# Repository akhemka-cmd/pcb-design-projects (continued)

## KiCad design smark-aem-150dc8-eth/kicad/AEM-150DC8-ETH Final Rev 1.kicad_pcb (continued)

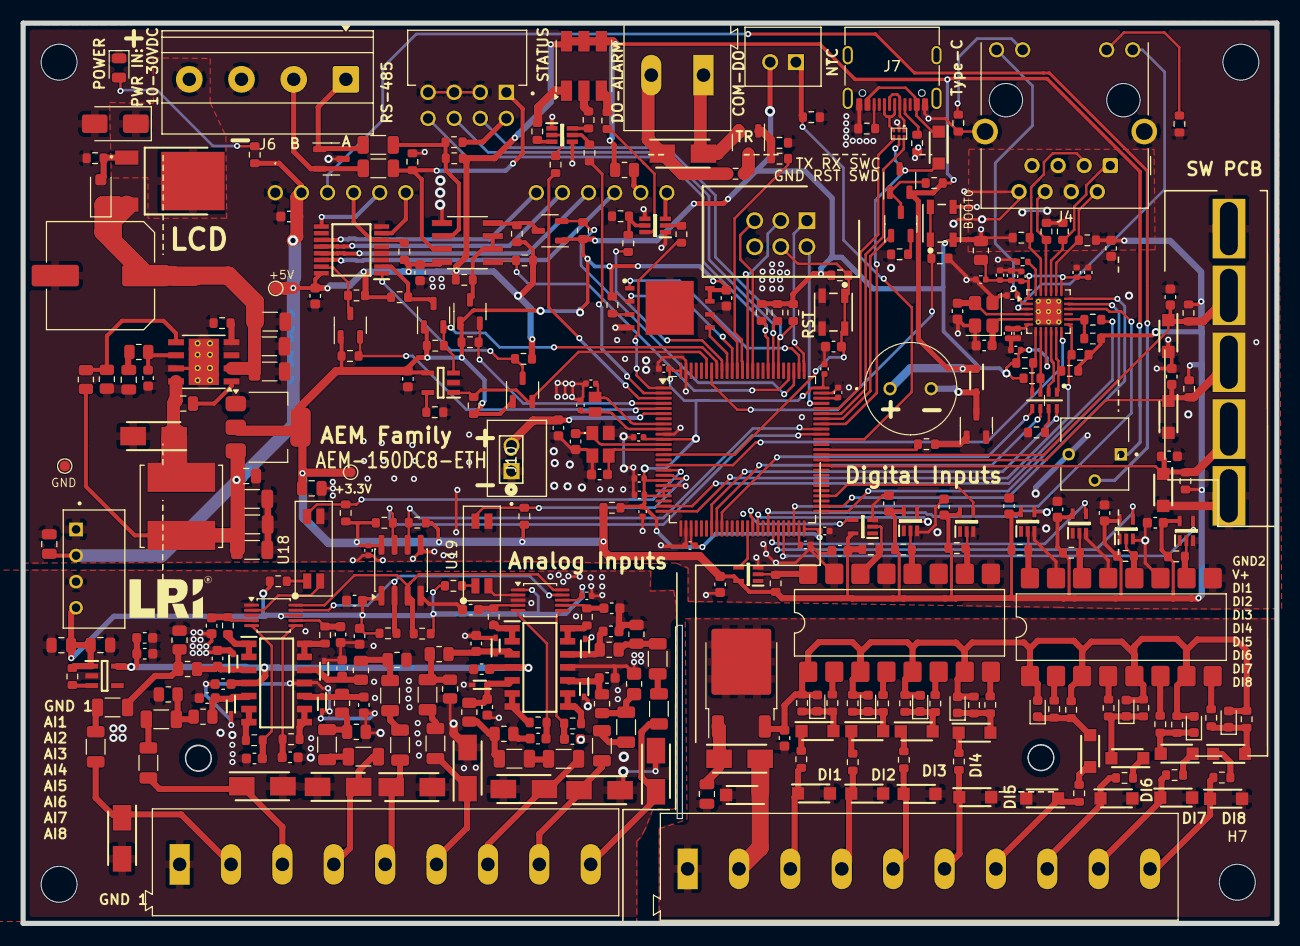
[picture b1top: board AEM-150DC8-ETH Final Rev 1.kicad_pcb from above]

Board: 2 copper layers, 122.0 x 87.6 mm, 360 parts (0 on the bottom side), 241 nets.

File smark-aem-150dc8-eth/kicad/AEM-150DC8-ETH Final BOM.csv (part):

#,Qty,Value,Reference,Footprint,Description,LCSC_Part,MPN,Manufacturer,PartLink,MANF_NUMBER
90,1,LCD 16x4,DS1,AEM-150DC8:NHD0416BZFLGBW,LCD Character Display Modules & Accessories STN- GRAY Transfl 87.0 x 60.0,,CH1604C,,,
56,1,Buzzer,BZ1,AEM-150DC8:QMB09B03,BUZZER MAGNETIC 2V~5V 9mm TH,C96256,QMB-09B-03,Huaneng,,
18,4,4.7K,"R120,R121,R122,R123",AEM-150DC8:R0603,,,,PANASONIC,,
107,2,1K,"R136,R142",AEM-150DC8:R0603,,,,PANASONIC,,
26,13,10K,"R101,R125,R126,R127,R128,R139,R140,R141,R143,R144,R152,R153,R236",AEM-150DC8:R0603,10kΩ ±5% 100mW 0603 Thick Film Resistor,C2907166,FRC0603J472 TS,FOJAN,,
76,1,FerriteBead,FB1,AEM-150DC8:R0805,Ferrite bead,,,,,
77,1,Screw_Terminal_01x02,J8,AEM-150DC8:TerminalBlock_2P_P5.08mm,"Generic screw terminal, single row, 01x02",C5188473,MX128L-5.08-02P-GN01-Cu-Y-A,MAX,,
57,1,100uF/63V,C2,Capacitor_SMD:C_Elec_10x10.2,CAP ALUM 100uF ±20% 63V SMD,C280414,RT1J101M1010,ROQANG,,
62,1,RJ45_Hanrun_HR911105A_Horizontal,J4,Connector_RJ:RJ45_Hanrun_HR911105A_Horizontal,CONN MOD JACK RJ45 TH,C12074,HR911105A,,,
129,1,USB_C_Receptacle_USB2.0_16P,J7,Connector_USB:USB_C_Receptacle_G-Switch_GT-USB-7010ASV,USB 2.0-only 16P Type-C Receptacle connector,C42400252,HYCW498-USBC16-735B,HOAUC,,
65,1,25Mhz Crystal,Y3,Crystal:Crystal_SMD_3225-4Pin_3.2x2.5mm,CRYSTAL 25MHz 12pF SMD,C9006,X322525MOB4SI,,,
49,1,SMAJ30A,D4,Diode_SMD:D_SMA,48.4VC Clamp 8.3A Ipp TVS DIODE DO-214AC(SMA),C908776,SMAJ30A,GOODWORK,,
73,1,BZT52C10,D8,Diode_SMD:D_SOD-123F,DIODE ZENER 10V 500mW SOD-123,C5182291,BZT52C10V,JUXING,,
68,1,RO-0505S_EHP,PS1,footprints:CONV_RO-0505S_H,DC/DC Converters - Through Hole 1W 05VIN 05VOUT CONV DC/DC,  C22372152 ,RO-0505S/EHP,RECOM,,
79,1,Screw_Terminal_01x02,J10,FT1:CONN2_M22-2010_HRW,"Generic screw terminal, single row, 01x02, script generated (kicad-library-utils/schlib/autogen/connector/)",,,,,
17,1,XL-5050RGBC,D55,LED_SMD:LED_RGB_5050-6,5050 RGB SMD LED,C2843868,XL-5050RGBC,XINGLIGHT,,
98,2,LTV-217,"U18,U19",LTV-217:LTV-217,Optocoupler DC-IN 1-CH Transistor DC-OUT 4-Pin SMD T/R,,"LTV-217-C-G,LTV217",,,LTV-217-C-G
89,1,LAN8742A,U27,Package_DFN_QFN:VQFN-24-1EP_4x4mm_P0.5mm_EP2.5x2.5mm_ThermalVias,"LAN8720 Ethernet PHY with RMII interface, QFN-24",,LAN8742A,,,
67,2,LTV-847S,"U3,U4",Package_DIP:SMDIP-16_W9.53mm,"DC Optocoupler, Vce 35V, CTR 50%, SMDIP-16",C114599,LTV-847S,LITEON,,
113,1,STM32F407VETx,U23,Package_QFP:LQFP-100_14x14mm_P0.5mm,"STMicroelectronics Arm Cortex-M4 MCU, 512KB flash, 192KB RAM, 168 MHz, 1.8-3.6V, 82 GPIO, LQFP100",C28730,STM32F407VET6,,,
83,1,ISO1540DR,U26,Package_SO:SOIC-8_3.9x4.9mm_P1.27mm,"I2C Isolator, 2.5 kVrms, Bidirectional clock and data, SOIC-8",,ISO1540DR,,,
42,1,TPS54360DDAR,U5,Package_SO:TI_SO-PowerPAD-8_ThermalVias,"3.5A, Step Down DC-DC Converter with Eco-mode, 4.5-60V Input Voltage, PowerSO-8",C44377,TPS54360DDAR,TI,,
122,2,ADS1115IDGS,"U24,U25",Package_SO:TSSOP-10_3x3mm_P0.5mm,"Ultra-Small, Low-Power, I2C-Compatible, 860-SPS, 16-Bit ADCs With Internal Reference, Oscillator, and Programmable Comparator, VSSOP-10",,ADS1115IDGS,,,
100,1,100K,R2,Resistor_SMD:R_0603_1608Metric,RES 100kΩ ±1% 100mW 0603,C2906980,FRC0603F1003TS,FOJAN,https://www.digikey.in/en/products/detail/yageo/RC0603FR-071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,
106,1,1K,R60,Resistor_SMD:R_0805_2012Metric,,,,PANASONIC,,
7,3,20.5K,"R57,R59,R61",Resistor_SMD:R_0805_2012Metric,,C161788,ERJPB6B1002V,PANASONIC,,
8,1,20.5K,R63,Resistor_SMD:R_0805_2012Metric_Pad1.20x1.40mm_HandSolder,,C161788,ERJPB6B1002V,PANASONIC,,
47,1,4.7uF/25V,C67,SMARKKicadLib:C0402,4.7uF ±20% 25V Ceramic Capacitor X5R 0402,C6119795,CGA0402X5R475M250GT,HRE,,
22,7,100nF,"C80,C115,C117,C119,C121,C122,C123",SMARKKicadLib:C0402,,C36911361,CGA0402X7R104M500GT,HRE,,
38,3,1uF,"C79,C81,C120",SMARKKicadLib:C0402,,C36911361,CGA0402X7R104M500GT,HRE,,
20,5,0.1uF,"C62,C65,C66,C69,C70",SMARKKicadLib:C0402,,,,HRE,https://www.digikey.in/en/products/detail/samsung-electro-me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 ,
32,2,12pF,"C73,C74",SMARKKicadLib:C0402,,,,HRE,,
28,2,10uF,"C64,C116",SMARKKicadLib:C0402,,,,HRE,https://www.digikey.in/en/products/detail/samsung-electro-me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 ,
50,1,6.8pF/100V,C17,SMARKKicadLib:C0603,6.8pF NP0 100V 0603 Ceramic Capacitors RoHS,C6117724,AC0603CRNPO0BN6R8,YAGEO,,
31,2,12pF,"C45,C46",SMARKKicadLib:C0603,12pF ±5% 50V Ceramic Capacitor C0G 0603,C45359931,CGA0603C0G120J500JT,HRE,,
37,4,1uF/10V,"C3,C56,C57,C58",SMARKKicadLib:C0603,1uF ±10% 10V Ceramic Capacitor X5R 0603,C20070307,CGA0603X5R105K100JT,HRE,,
27,1,10uF,C63,SMARKKicadLib:C0603,10uF ±10% 50V Ceramic Capacitor X7R 0603,C6119867,CGA0603X7R104K500JT,HRE,https://www.digikey.in/en/products/detail/samsung-electro-me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 ,
59,1,10uF/16V,C72,SMARKKicadLib:C0603,CAP CER 10uF 16V X5R 0603,,,,,
19,34,0.1uF,"C4,C5,C6,C7,C9,C13,C14,C15,C16,C19,C20,C21,C22,C24,C27,C28,C29,C30,C31,C32,C33,C34,C37,C38,C39,C40,C42,C48,C54,C55,C59,C60,C61,C75",SMARKKicadLib:C0603,0.1uF ±10% 50V Ceramic Capacitor X7R 0603,C6119867,,HRE,https://www.digikey.in/en/products/detail/samsung-electro-me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 ,
23,1,100nF/25V,C18,SMARKKicadLib:C0805,100nF ±10% 25V Ceramic Capacitor X7R 0805,C36911366,CGA0805X7R104K250KT,HRE,,
60,1,10uF/50V,C1,SMARKKicadLib:C0805,CAP CER 10uF 50V X5R 0805,C2932476,CL21A106KBYQNNE,Samsung Electro-Mechanics,,
58,3,10uF/16V,"C25,C36,C77",SMARKKicadLib:C0805,CAP CER 10uF 16V X5R 0805,C77075,GRM21BR61C106KE15L,FOJAN,,
46,1,4.7nF/50V,C12,SMARKKicadLib:C0805,4.7nF ±20% 50V Ceramic Capacitor X7R 0805,C5375827,TCC0805X7R472M500DT,CCTC,,
36,3,1uF/100V,"C8,C10,C11",SMARKKicadLib:C1206,1uF ±10% 100V Ceramic Capacitor X7R 1206,C13832,CL31B105KCHNNNE,Samsung Electro-Mechanics,,
61,3,47uF/10V,"C23,C26,C35",SMARKKicadLib:C1206,CAP CER 47uF 10V X5R 1206,C5449028,TCC1206X5R476K100HT,CCTC,,
16,1,33R,RN1,SMARKKicadLib:CAT16-1206_8L,"4 resistor network, parallel topology, split",,CAT16-1206_8L,,,
55,1,CONN_03X2SHROUD,J5,SMARKKicadLib:CONN_2X3-SHROUDED_HEADER,"Box Header, Vertical, 6 Pos",C601936,321006SG0ABK00A01,JILN,https://www.digikey.in/en/products/detail/adam-tech/BHR-06-V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,
52,1,B340A-13-F,D6,SMARKKicadLib:DO-214AC,80A 1 Independent 40V 500mV@3A 3A SMA(DO-214AC) Single Diodes RoHS,C85098,B340A-13-F,DIODES,https://www.digikey.in/en/products/detail/diodes-incorporate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,
117,8,SMAJ160A,"D11,D12,D13,D14,D37,D38,D39,D40",SMARKKicadLib:DO-214AC,TVS DIODE 160VWM 259VC DO-214AC(SMA),C2984997,SMAJ160A,GOODWORK,,
48,1,SMAJ26A,D49,SMARKKicadLib:DO-214AC,42.1VC Clamp 9.5A@10/1000us Ipp DO-214AC(SMA),C42370520,SMAJ26A,TECH PUBLIC,,
72,1,SS54,D41,SMARKKicadLib:DO-214AC,Diode Independent 40V 5A Surface Mount SMA(DO-214AC),C2988633,UMW SS54A,UMW,,
121,1,PRTR5V0U2F,D50,SMARKKicadLib:FNL6_SOT886_NEX,TVS DIODE 5.5VWM 6XSON,C478118,"PRTR5V0U2F,115",Nexperia USA Inc.,https://www.digikey.in/en/products/detail/nexperia-usa-inc/P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,
1,1,MNR8065T100MT,L1,SMARKKicadLib:IND_SRN8040TA,,,MNR8065T100MT,MetalLions,,
63,1,Conn_01x02,J1,SMARKKicadLib:JST_B2B-XH-A,Connector Header 2 position 2.54mm Pitch 3A Through Hole -25℃~+85℃,C42391660,HX-XH2.54-2PZZ,hanxia,,
78,1,Screw_Terminal_01x02,J9,SMARKKicadLib:JST_B2B-XH-A,"Generic screw terminal, single row, 01x02, script generated (kicad-library-utils/schlib/autogen/connector/)",,,,,
91,8,LED,"D1,D2,D5,D7,D9,D10,D15,D16",SMARKKicadLib:LED_0603_1608Metric,LED RED CLEAR CHIP SMD 0603,C965799,XL-1608SURC-06,XINGLIGHT,https://www.digikey.in/en/products/detail/liteon/LTST-C190KR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,
92,1,LED,D46,SMARKKicadLib:LED_0805_2012Metric,LED RED WATER CLEAR 0805 SMD,C22371391,XL-2012SURC,XINGLIGHT,,
54,2,MountingHole,"H2,H3",SMARKKicadLib:MountingHole_2.5mm,"Board Spacers, Standoffs RoHS",C123695,HP-20M3*20,HIWA,,
99,1,10K,RV1,SMARKKicadLib:Pot_TRIM_3362P-1-103LF,POT 10kΩ Through Hole,C118956,3362P-1-103LF,BOCHEN,,
101,2,100K,"R89,R103",SMARKKicadLib:R0603,RES 100kΩ ±1% 100mW 0603,C2906980,FRC0603F1003TS,FOJAN,https://www.digikey.in/en/products/detail/yageo/RC0603FR-071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,
103,1,150R,R108,SMARKKicadLib:R0603,RES 150Ω ±1% 100mW 0603,C2906994,FRC0603F1500TS,FOJAN,,
33,1,191K,R44,SMARKKicadLib:R0603,191kΩ ±1% 100mW 0603 Thick Film Resistor,C2974031,FRC0603F1913TS,FOJAN,,
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
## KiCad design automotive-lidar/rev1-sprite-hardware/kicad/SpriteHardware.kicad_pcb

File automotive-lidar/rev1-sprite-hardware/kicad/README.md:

# Hardware

KiCad files for Project Sprite

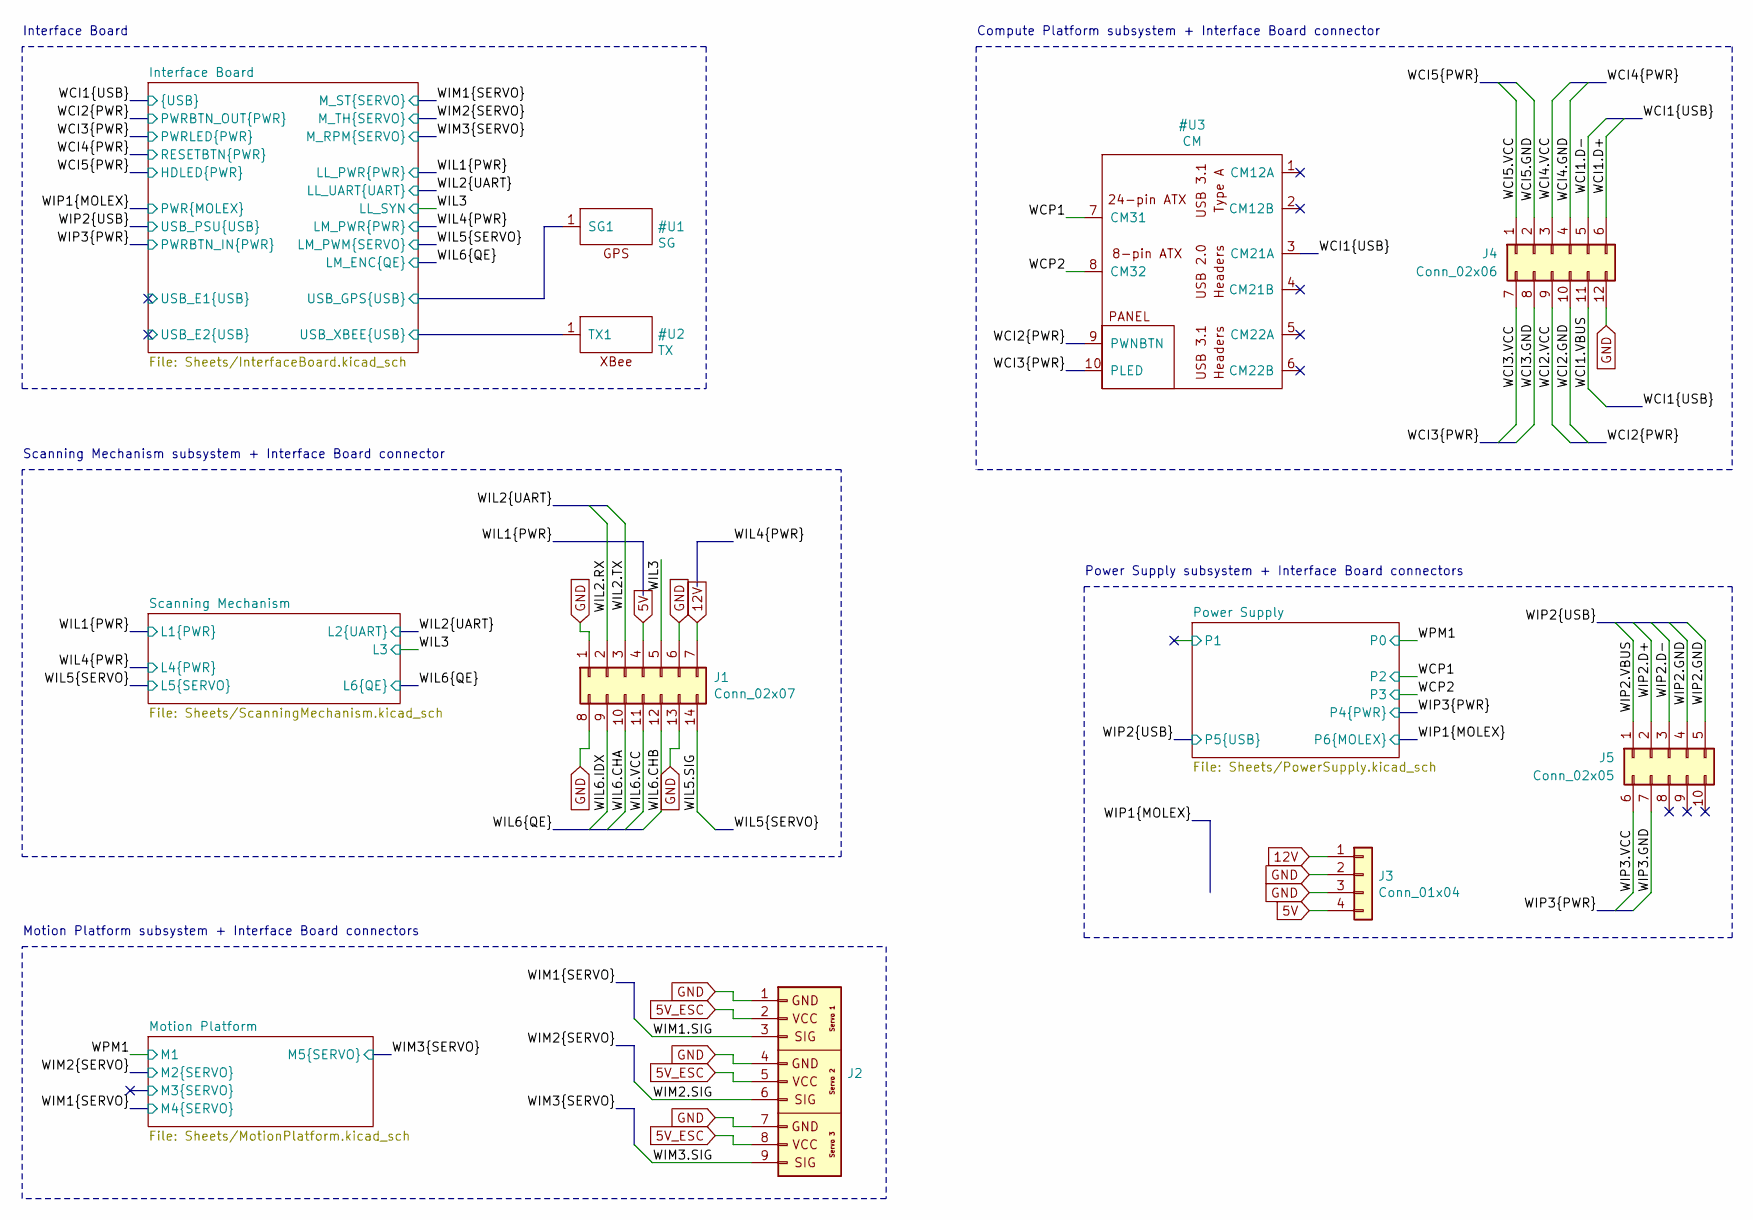
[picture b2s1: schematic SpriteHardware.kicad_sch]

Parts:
J1: Conn_02x07; 901303314
J2: Conn_03x03_Servo
J3: Conn_01x04; 641737-1
J4: Conn_02x06; 901303312
J5: Conn_02x05; 901303310

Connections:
5V: J1.4, J3.4; also elsewhere on the board
5V_ESC: J2.2 (VCC1), J2.5 (VCC2), J2.8 (VCC3); also elsewhere on the board
12V: J1.7, J3.1
/WCI1.D+: J4.6; also elsewhere on the board
/WCI1.D-: J4.5; also elsewhere on the board
/WCI1.VBUS: J4.11; also elsewhere on the board
/WCI3.GND: J4.8; also elsewhere on the board
/WCI3.VCC: J4.7; also elsewhere on the board
/WCI4.GND: J4.4; also elsewhere on the board
/WCI4.VCC: J4.3; also elsewhere on the board
/WCI5.GND: J4.2; also elsewhere on the board
/WCI5.VCC: J4.1; also elsewhere on the board
/WIL2.RX: J1.2; also elsewhere on the board
/WIL2.TX: J1.3; also elsewhere on the board
/WIL3: J1.5; also elsewhere on the board
/WIL5.SIG: J1.14; also elsewhere on the board
/WIL6.CHA: J1.10; also elsewhere on the board
/WIL6.CHB: J1.12; also elsewhere on the board
/WIL6.IDX: J1.9; also elsewhere on the board
/WIL6.VCC: J1.11; also elsewhere on the board
/WIM1.SIG: J2.3 (SIG1); also elsewhere on the board
/WIM2.SIG: J2.6 (SIG2); also elsewhere on the board
/WIM3.SIG: J2.9 (SIG3); also elsewhere on the board
/WIP2.D+: J5.2; also elsewhere on the board
/WIP2.D-: J5.3; also elsewhere on the board
/WIP2.GND: J5.4, J5.5
/WIP2.VBUS: J5.1; also elsewhere on the board
GND: J1.1, J1.6, J1.8, J1.13, J2.1 (GND1), J2.4 (GND2), J2.7 (GND3), J3.2, J3.3, J4.12; also elsewhere on the board

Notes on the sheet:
Motion Platform subsystem + Interface Board connectors
Compute Platform subsystem + Interface Board connector
Interface Board
Power Supply subsystem + Interface Board connectors
Scanning Mechanism subsystem + Interface Board connector

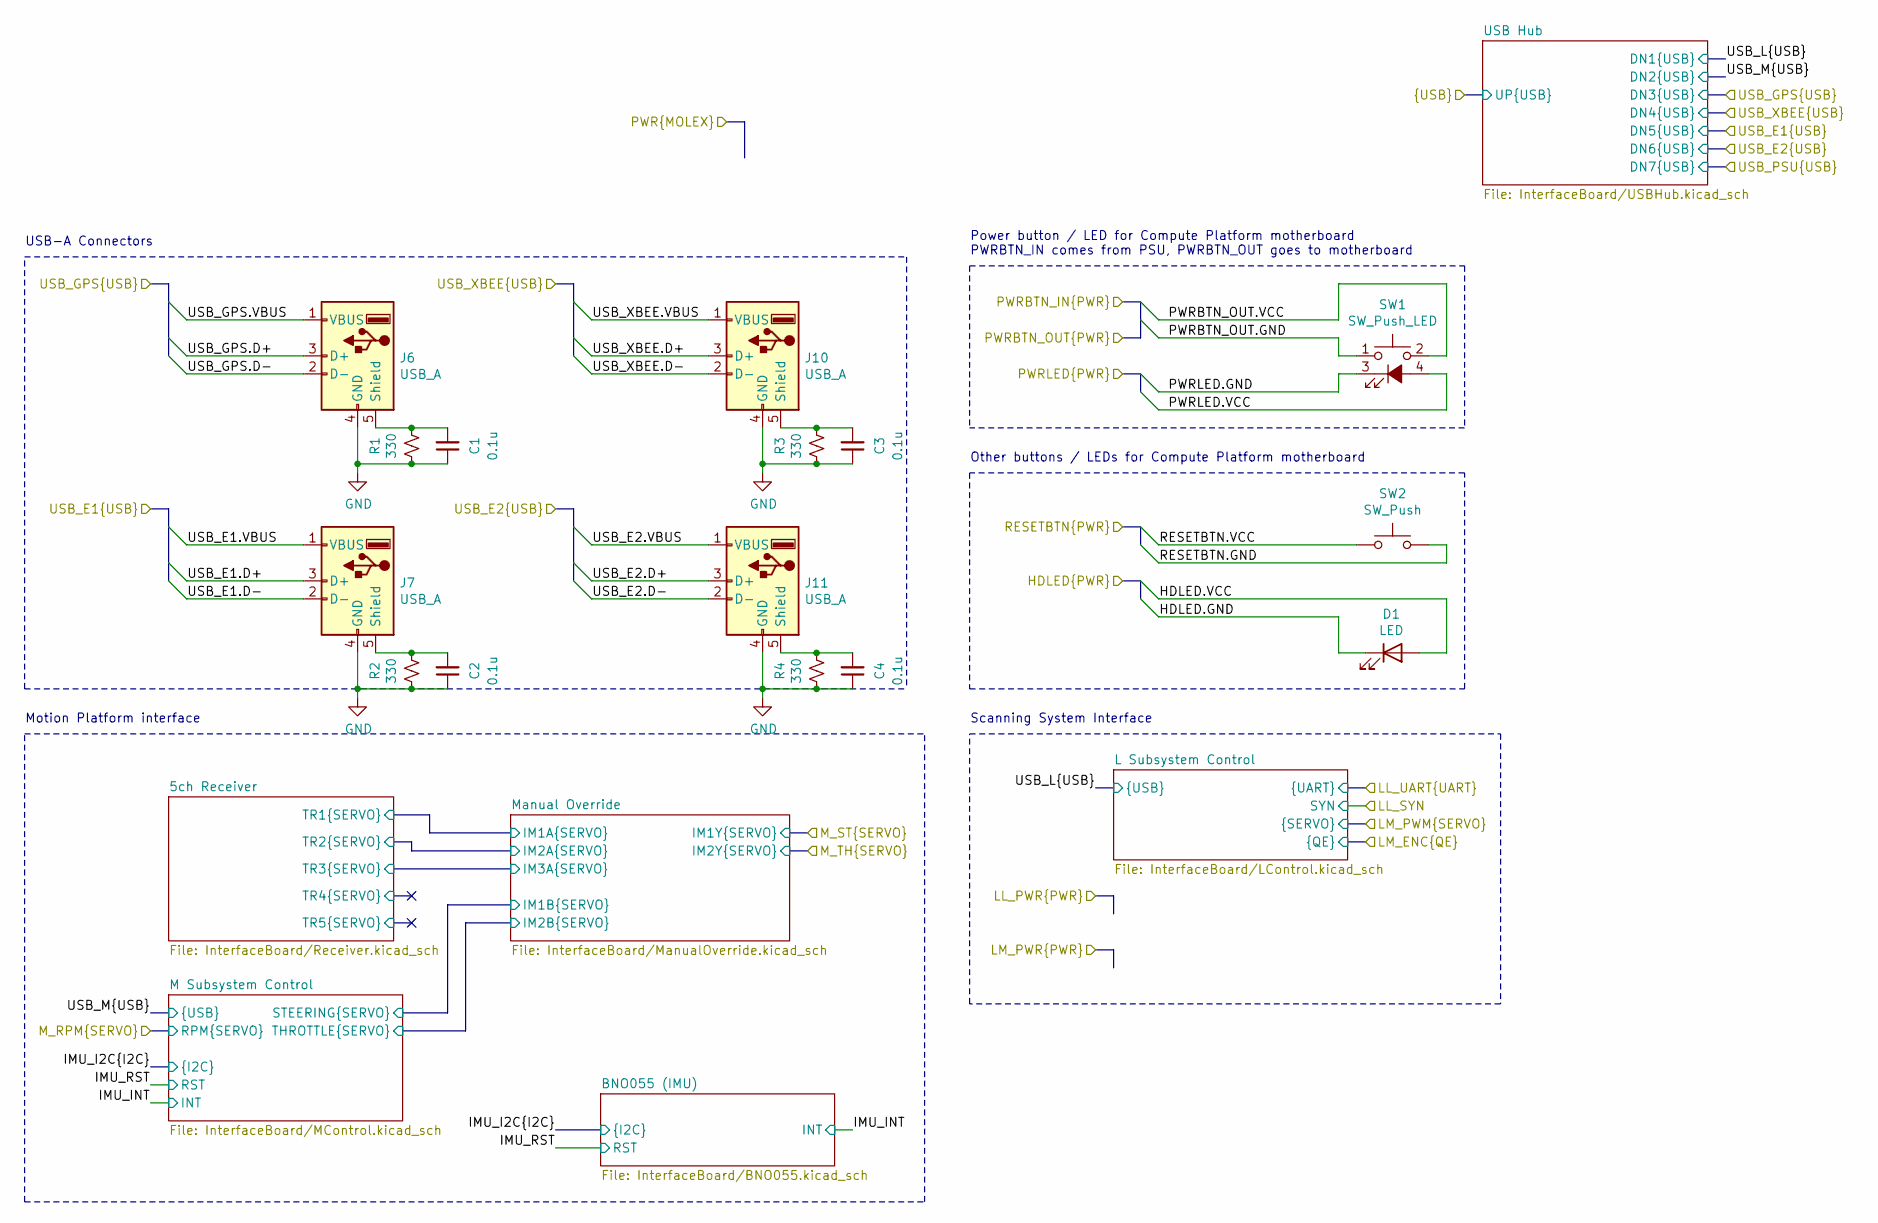
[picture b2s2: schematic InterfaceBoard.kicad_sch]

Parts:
C1, C2, C3, C4: 0.1u; C_0603_1608Metric_Pad1.05x0.95mm_HandSolder
D1: LED; LED_0603_1608Metric_Pad1.05x0.95mm_HandSolder
J6, J7, J10, J11: USB_A; USB_A_Female_Vertical_RA_73725-0110BLF
R1, R2, R3, R4: 330; R_0603_1608Metric_Pad1.05x0.95mm_HandSolder
SW1: SW_Push_LED; 3105
SW2: SW_Push; SW_SPST_PTS645

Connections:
/USB_E1.D+: J7.3 (D+); also elsewhere on the board
/USB_E1.D-: J7.2 (D-); also elsewhere on the board
/USB_E1.VBUS: J7.1 (VBUS); also elsewhere on the board
/USB_E2.D+: J11.3 (D+); also elsewhere on the board
/USB_E2.D-: J11.2 (D-); also elsewhere on the board
/USB_E2.VBUS: J11.1 (VBUS); also elsewhere on the board
/USB_GPS.D+: J6.3 (D+); also elsewhere on the board
/USB_GPS.D-: J6.2 (D-); also elsewhere on the board
/USB_GPS.VBUS: J6.1 (VBUS); also elsewhere on the board
/USB_XBEE.D+: J10.3 (D+); also elsewhere on the board
/USB_XBEE.D-: J10.2 (D-); also elsewhere on the board
/USB_XBEE.VBUS: J10.1 (VBUS); also elsewhere on the board
/WCI3.GND: SW1.3 (K); also elsewhere on the board
/WCI3.VCC: SW1.4 (A); also elsewhere on the board
/WCI4.GND: SW2.2; also elsewhere on the board
/WCI4.VCC: SW2.1; also elsewhere on the board
/WCI5.GND: D1.1 (K); also elsewhere on the board
/WCI5.VCC: D1.2 (A); also elsewhere on the board
GND: C1.1, C2.1, C3.1, C4.1, J6.4 (GND), J7.4 (GND), J10.4 (GND), J11.4 (GND), R1.1, R2.1, R3.1, R4.1; also elsewhere on the board
unnamed: C1.2, J6.5 (Shield), R1.2
unnamed: C2.2, J7.5 (Shield), R2.2
unnamed: C3.2, J10.5 (Shield), R3.2
unnamed: C4.2, J11.5 (Shield), R4.2

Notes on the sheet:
Scanning System Interface
Power button / LED for Compute Platform motherboard PWRBTN_IN comes from PSU, PWRBTN_OUT goes to motherboard
USB-A Connectors
Other buttons / LEDs for Compute Platform motherboard
Motion Platform interface

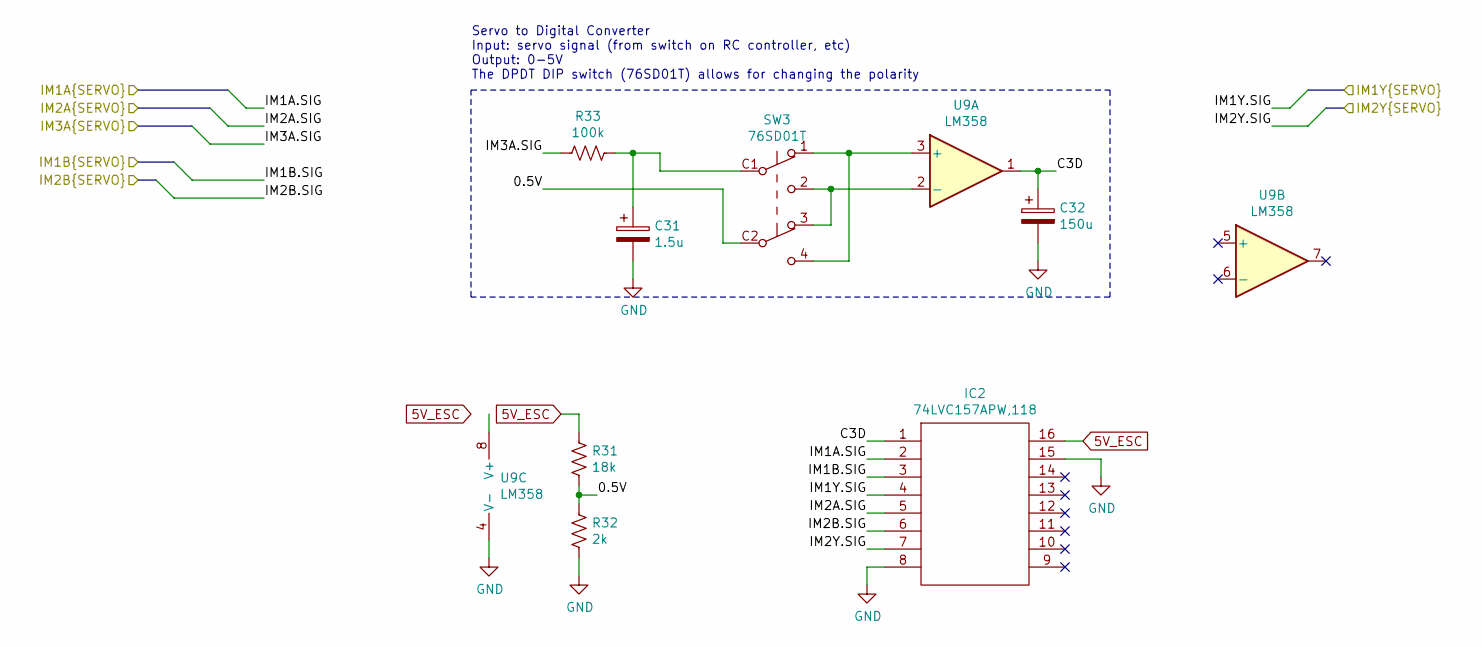
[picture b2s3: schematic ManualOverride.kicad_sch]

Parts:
C31: 1.5u; C_0805_2012Metric_Pad1.15x1.40mm_HandSolder
C32: 150u; CP_Elec_6.3x5.4_Nichicon
IC2: 74LVC157APW,118; SOP65P640X110-16N; Mouser Part Number 771-74LVC157APW-T
R31: 18k; R_0603_1608Metric_Pad1.05x0.95mm_HandSolder
R32: 2k; R_0603_1608Metric_Pad1.05x0.95mm_HandSolder
R33: 100k; R_0603_1608Metric_Pad1.05x0.95mm_HandSolder
SW3: 76SD01T
U9: LM358; SOIC127P600X175-8N

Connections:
5V_ESC: IC2.16, R31.1; also elsewhere on the board
/Interface Board/IM2A.SIG: IC2.5; also elsewhere on the board
/Interface Board/IM3A.SIG: R33.2; also elsewhere on the board
/Interface Board/Manual Override/0.5V: R31.2, R32.1, SW3.C2 (B)
/Interface Board/Manual Override/C3D: C32.1, IC2.1, U9.1
/Interface Board/STEERING.SIG: IC2.3; also elsewhere on the board
/Interface Board/THROTTLE.SIG: IC2.6; also elsewhere on the board
/Interface Board/TR1.SIG: IC2.2; also elsewhere on the board
/WIM1.SIG: IC2.4; also elsewhere on the board
/WIM2.SIG: IC2.7; also elsewhere on the board
GND: C31.2, C32.2, IC2.8, IC2.15, R32.2, U9.4 (V-); also elsewhere on the board
unnamed: C31.1, R33.1, SW3.C1 (B)
unnamed: SW3.1 (A), SW3.4 (C), U9.3 (+)
unnamed: SW3.2 (C), SW3.3 (A), U9.2 (-)

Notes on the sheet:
Servo to Digital Converter Input: servo signal (from switch on RC controller, etc) Output: 0-5V The DPDT DIP switch (76SD01T) allows for changing the polarity

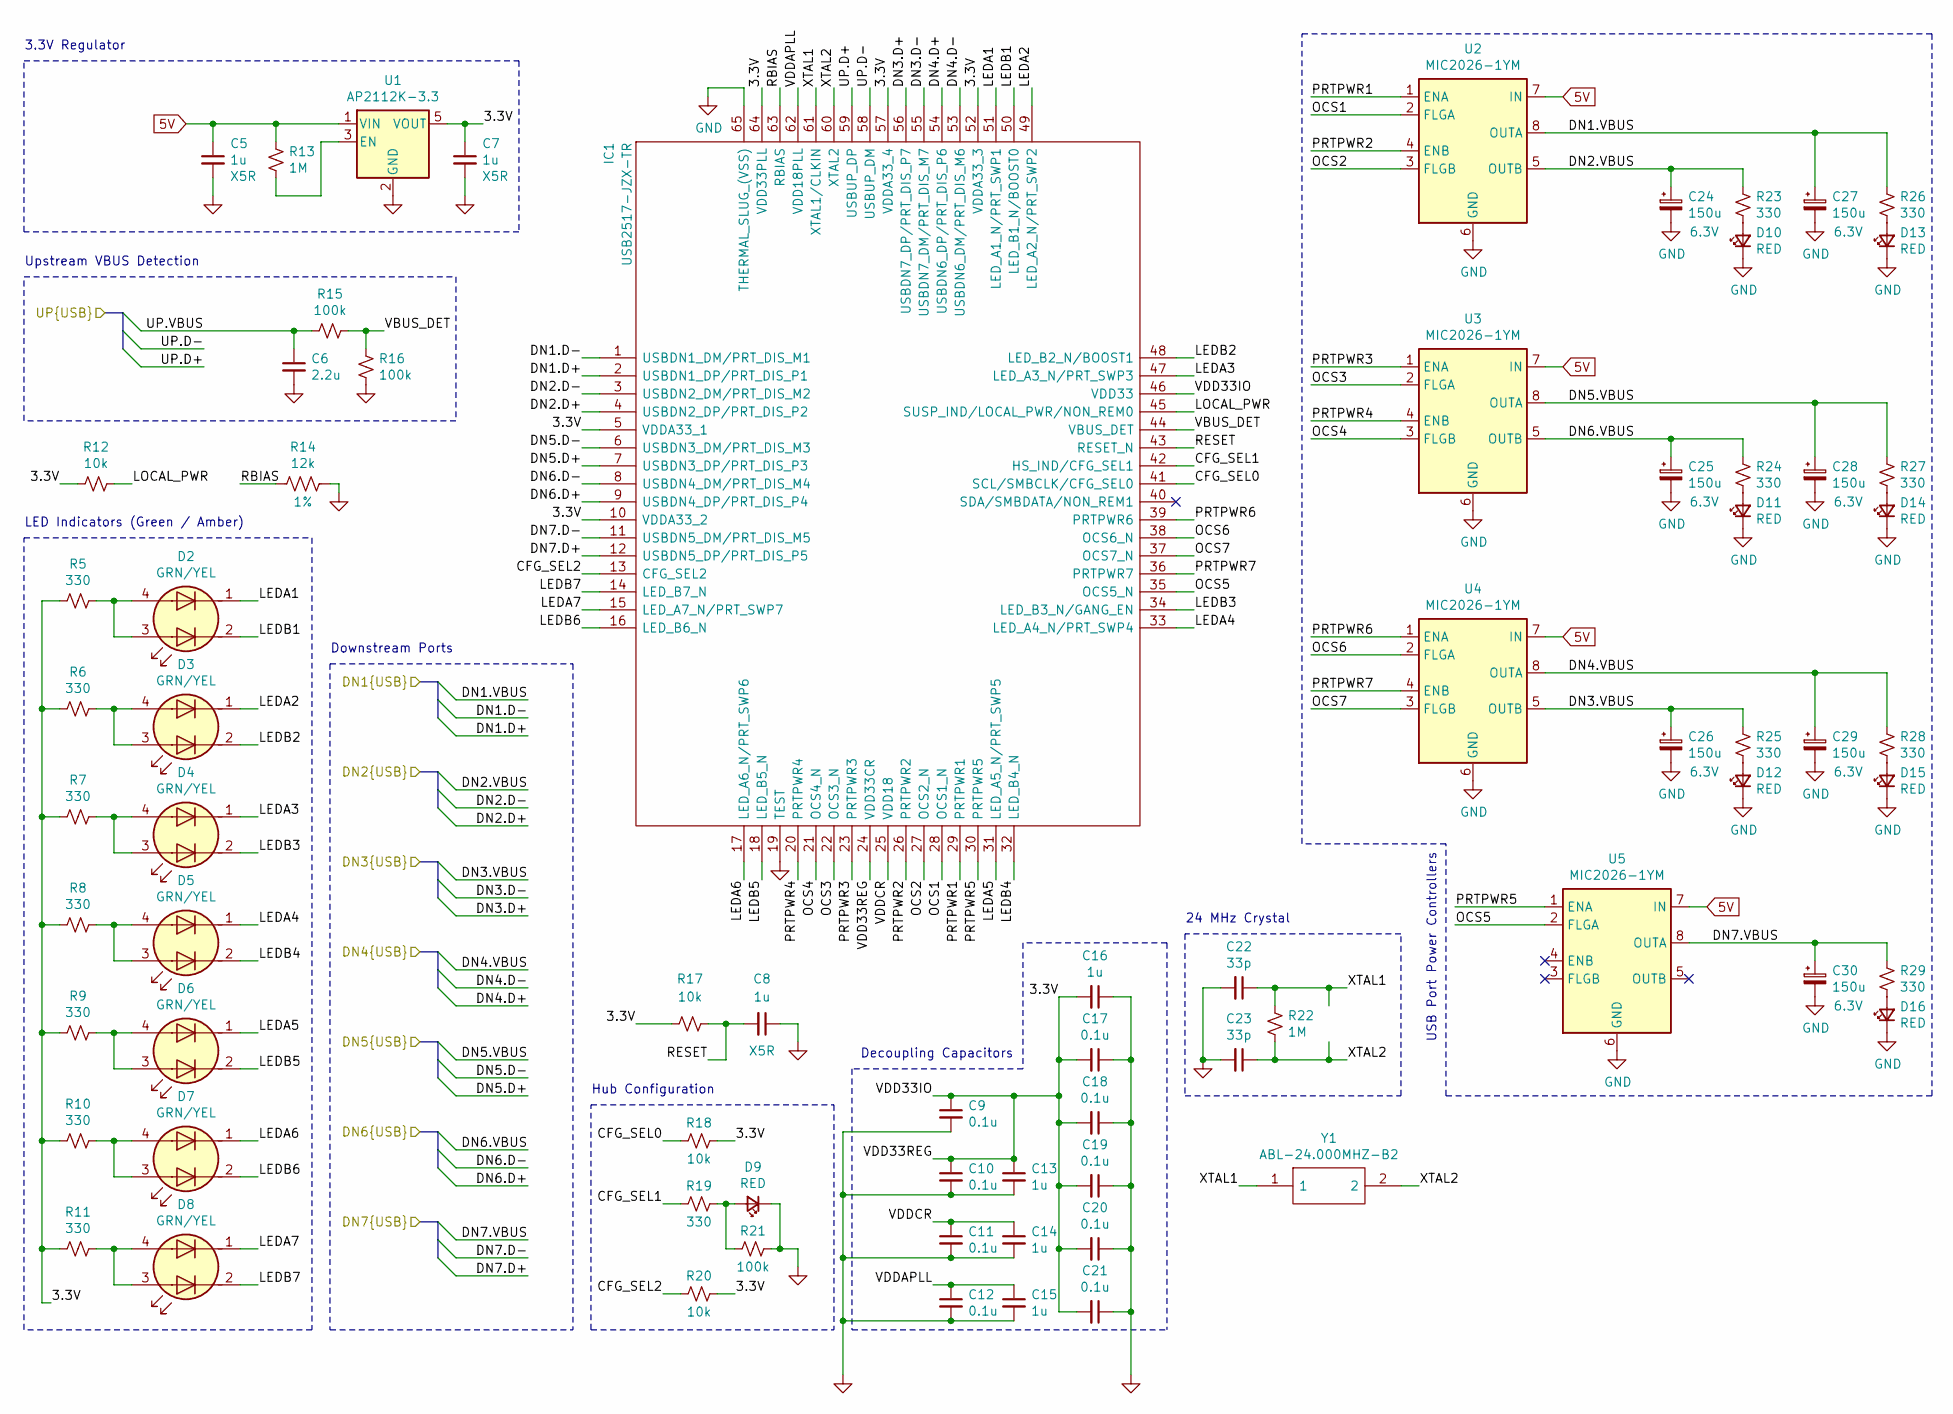
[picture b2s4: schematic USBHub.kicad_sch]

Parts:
C5, C7, C13, C14, C15, C16: 1u; C_0603_1608Metric_Pad1.05x0.95mm_HandSolder
C6: 2.2u; C_0603_1608Metric_Pad1.05x0.95mm_HandSolder
C8: 1u; C_0603_1608Metric_Pad1.05x0.95mm_HandSolder; Rating X5R
C9, C10, C11, C12, C17, C18, C19, C20, C21: 0.1u; C_0603_1608Metric_Pad1.05x0.95mm_HandSolder
C22, C23: 33p; C_0603_1608Metric_Pad1.05x0.95mm_HandSolder
C24, C25, C26, C27, C28, C29, C30: 150u; CP_Elec_6.3x5.4_Nichicon; Voltage 6.3V
D2, D3, D4, D5, D6, D7, D8: GRN/YEL; 156125YV73000
D9, D10, D11, D12, D13, D14, D15, D16: RED; LED_0603_1608Metric_Pad1.05x0.95mm_HandSolder
IC1: USB2517-JZX-TR; QFN50P900X900X100-65N-D; Mouser Part Number 579-USB2517-JZX-TR
R5, R6, R7, R8, R9, R10, R11, R19, R23, R24, R25, R26, R27, R28, R29: 330; R_0603_1608Metric_Pad1.05x0.95mm_HandSolder
R12, R17, R18, R20: 10k; R_0603_1608Metric_Pad1.05x0.95mm_HandSolder
R13, R22: 1M; R_0603_1608Metric_Pad1.05x0.95mm_HandSolder
R14: 12k; R_0603_1608Metric_Pad1.05x0.95mm_HandSolder; Tolerance 1%
R15, R16, R21: 100k; R_0603_1608Metric_Pad1.05x0.95mm_HandSolder
U1: AP2112K-3.3; SOT-23-5
U2, U3, U4, U5: MIC2026-1YM; SOIC-8_3.9x4.9mm_P1.27mm
Y1: ABL-24.000MHZ-B2; ABL110592MHZB2; Manufacturer_Part_Number ABL-24.000MHZ-B2; Mouser Part Number 815-ABL-24-B2

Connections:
5V: C5.1, R13.2, U1.1 (VIN), U2.7 (IN), U3.7 (IN), U4.7 (IN), U5.7 (IN); also elsewhere on the board
/Interface Board/USB Hub/3.3V: C7.1, C9.1, C10.1, C13.1, C16.2, C17.2, C18.2, C19.2, C20.2, C21.2, IC1.5 (VDDA33_1), IC1.10 (VDDA33_2), IC1.24 (VDD33CR), IC1.46 (VDD33), IC1.52 (VDDA33_3), IC1.57 (VDDA33_4), IC1.64 (VDD33PLL), R5.2, R6.2, R7.2, R8.2, R9.2, R10.2, R11.2, R12.2, R17.2, R18.1, R20.1, U1.5 (VOUT)
/Interface Board/USB Hub/CFG_SEL0: IC1.41 (SCL/SMBCLK/CFG_SEL0), R18.2
/Interface Board/USB Hub/CFG_SEL1: IC1.42 (HS_IND/CFG_SEL1), R19.2
/Interface Board/USB Hub/CFG_SEL2: IC1.13 (CFG_SEL2), R20.2
/Interface Board/USB Hub/LEDA1: D2.1 (A2), IC1.51 (LED_A1_N/PRT_SWP1)
/Interface Board/USB Hub/LEDA2: D3.1 (A2), IC1.49 (LED_A2_N/PRT_SWP2)
/Interface Board/USB Hub/LEDA3: D4.1 (A2), IC1.47 (LED_A3_N/PRT_SWP3)
/Interface Board/USB Hub/LEDA4: D5.1 (A2), IC1.33 (LED_A4_N/PRT_SWP4)
/Interface Board/USB Hub/LEDA5: D6.1 (A2), IC1.31 (LED_A5_N/PRT_SWP5)
/Interface Board/USB Hub/LEDA6: D7.1 (A2), IC1.17 (LED_A6_N/PRT_SWP6)
/Interface Board/USB Hub/LEDA7: D8.1 (A2), IC1.15 (LED_A7_N/PRT_SWP7)
/Interface Board/USB Hub/LEDB1: D2.2 (A1), IC1.50 (LED_B1_N/BOOST0)
/Interface Board/USB Hub/LEDB2: D3.2 (A1), IC1.48 (LED_B2_N/BOOST1)
/Interface Board/USB Hub/LEDB3: D4.2 (A1), IC1.34 (LED_B3_N/GANG_EN)
/Interface Board/USB Hub/LEDB4: D5.2 (A1), IC1.32 (LED_B4_N)
/Interface Board/USB Hub/LEDB5: D6.2 (A1), IC1.18 (LED_B5_N)
/Interface Board/USB Hub/LEDB6: D7.2 (A1), IC1.16 (LED_B6_N)
/Interface Board/USB Hub/LEDB7: D8.2 (A1), IC1.14 (LED_B7_N)
/Interface Board/USB Hub/LOCAL_PWR: IC1.45 (SUSP_IND/LOCAL_PWR/NON_REM0), R12.1
/Interface Board/USB Hub/OCS1: IC1.28 (OCS1_N), U2.2 (FLGA)
/Interface Board/USB Hub/OCS2: IC1.27 (OCS2_N), U2.3 (FLGB)
/Interface Board/USB Hub/OCS3: IC1.22 (OCS3_N), U3.2 (FLGA)
/Interface Board/USB Hub/OCS4: IC1.21 (OCS4_N), U3.3 (FLGB)
/Interface Board/USB Hub/OCS5: IC1.35 (OCS5_N), U5.2 (FLGA)
/Interface Board/USB Hub/OCS6: IC1.38 (OCS6_N), U4.2 (FLGA)
/Interface Board/USB Hub/OCS7: IC1.37 (OCS7_N), U4.3 (FLGB)
/Interface Board/USB Hub/PRTPWR1: IC1.29 (PRTPWR1), U2.1 (ENA)
/Interface Board/USB Hub/PRTPWR2: IC1.26 (PRTPWR2), U2.4 (ENB)
/Interface Board/USB Hub/PRTPWR3: IC1.23 (PRTPWR3), U3.1 (ENA)
/Interface Board/USB Hub/PRTPWR4: IC1.20 (PRTPWR4), U3.4 (ENB)
/Interface Board/USB Hub/PRTPWR5: IC1.30 (PRTPWR5), U5.1 (ENA)
/Interface Board/USB Hub/PRTPWR6: IC1.39 (PRTPWR6), U4.1 (ENA)
/Interface Board/USB Hub/PRTPWR7: IC1.36 (PRTPWR7), U4.4 (ENB)
/Interface Board/USB Hub/RBIAS: IC1.63 (RBIAS), R14.2
/Interface Board/USB Hub/RESET: C8.2, IC1.43 (RESET_N), R17.1
/Interface Board/USB Hub/VBUS_DET: IC1.44 (VBUS_DET), R15.1, R16.2
/Interface Board/USB Hub/VDDAPLL: C12.1, C15.1, IC1.62 (VDD18PLL)
/Interface Board/USB Hub/VDDCR: C11.1, C14.1, IC1.25 (VDD18)
/Interface Board/USB Hub/XTAL1: C22.1, IC1.61 (XTAL1/CLKIN), R22.1, Y1.1
/Interface Board/USB Hub/XTAL2: C23.1, IC1.60 (XTAL2), R22.2, Y1.2
/Interface Board/USB_L.D+: IC1.2 (USBDN1_DP/PRT_DIS_P1); also elsewhere on the board
/Interface Board/USB_L.D-: IC1.1 (USBDN1_DM/PRT_DIS_M1); also elsewhere on the board
/Interface Board/USB_M.D+: IC1.4 (USBDN2_DP/PRT_DIS_P2); also elsewhere on the board
/Interface Board/USB_M.D-: IC1.3 (USBDN2_DM/PRT_DIS_M2); also elsewhere on the board
/USB_E1.D+: IC1.7 (USBDN3_DP/PRT_DIS_P3); also elsewhere on the board
/USB_E1.D-: IC1.6 (USBDN3_DM/PRT_DIS_M3); also elsewhere on the board
/USB_E1.VBUS: C28.1, R27.2, U3.8 (OUTA); also elsewhere on the board
/USB_E2.D+: IC1.9 (USBDN4_DP/PRT_DIS_P4); also elsewhere on the board
/USB_E2.D-: IC1.8 (USBDN4_DM/PRT_DIS_M4); also elsewhere on the board
/USB_E2.VBUS: C25.1, R24.2, U3.5 (OUTB); also elsewhere on the board
/USB_GPS.D+: IC1.56 (USBDN7_DP/PRT_DIS_P7); also elsewhere on the board
/USB_GPS.D-: IC1.55 (USBDN7_DM/PRT_DIS_M7); also elsewhere on the board
/USB_GPS.VBUS: C26.1, R25.2, U4.5 (OUTB); also elsewhere on the board
/USB_XBEE.D+: IC1.54 (USBDN6_DP/PRT_DIS_P6); also elsewhere on the board
/USB_XBEE.D-: IC1.53 (USBDN6_DM/PRT_DIS_M6); also elsewhere on the board
/USB_XBEE.VBUS: C29.1, R28.2, U4.8 (OUTA); also elsewhere on the board
/WCI1.D+: IC1.59 (USBUP_DP); also elsewhere on the board
/WCI1.D-: IC1.58 (USBUP_DM); also elsewhere on the board
/WCI1.VBUS: C6.1, R15.2; also elsewhere on the board
/WIL6.VCC: C27.1, R26.2, U2.8 (OUTA); also elsewhere on the board
/WIM3.VCC: C24.1, R23.2, U2.5 (OUTB); also elsewhere on the board
/WIP2.D+: IC1.12 (USBDN5_DP/PRT_DIS_P5); also elsewhere on the board
/WIP2.D-: IC1.11 (USBDN5_DM/PRT_DIS_M5); also elsewhere on the board
/WIP2.VBUS: C30.1, R29.2, U5.8 (OUTA); also elsewhere on the board
GND: C5.2, C6.2, C7.2, C8.1, C9.2, C10.2, C11.2, C12.2, C13.2, C14.2, C15.2, C16.1, C17.1, C18.1, C19.1, C20.1, C21.1, C22.2, C23.2, C24.2, C25.2, C26.2, C27.2, C28.2, C29.2, C30.2, D9.1 (K), D10.1 (K), D11.1 (K), D12.1 (K), D13.1 (K), D14.1 (K), D15.1 (K), D16.1 (K), IC1.19 (TEST), IC1.65 (THERMAL_SLUG_(VSS)), R14.1, R16.1, R21.1, U1.2 (GND), U2.6 (GND), U3.6 (GND), U4.6 (GND), U5.6 (GND); also elsewhere on the board
unnamed: D2.3 (K1), D2.4 (K2), R5.1
unnamed: D3.3 (K1), D3.4 (K2), R6.1
unnamed: D4.3 (K1), D4.4 (K2), R7.1
unnamed: D5.3 (K1), D5.4 (K2), R8.1
unnamed: D6.3 (K1), D6.4 (K2), R9.1
unnamed: D7.3 (K1), D7.4 (K2), R10.1
unnamed: D8.3 (K1), D8.4 (K2), R11.1
unnamed: D9.2 (A), R19.1, R21.2
unnamed: D10.2 (A), R23.1
unnamed: D11.2 (A), R24.1
unnamed: D12.2 (A), R25.1
unnamed: D13.2 (A), R26.1
unnamed: D14.2 (A), R27.1
unnamed: D15.2 (A), R28.1
unnamed: D16.2 (A), R29.1
unnamed: R13.1, U1.3 (EN)

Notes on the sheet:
24 MHz Crystal
Upstream VBUS Detection
USB Port Power Controllers
Hub Configuration
LED Indicators (Green / Amber)
Decoupling Capacitors
Downstream Ports
3.3V Regulator

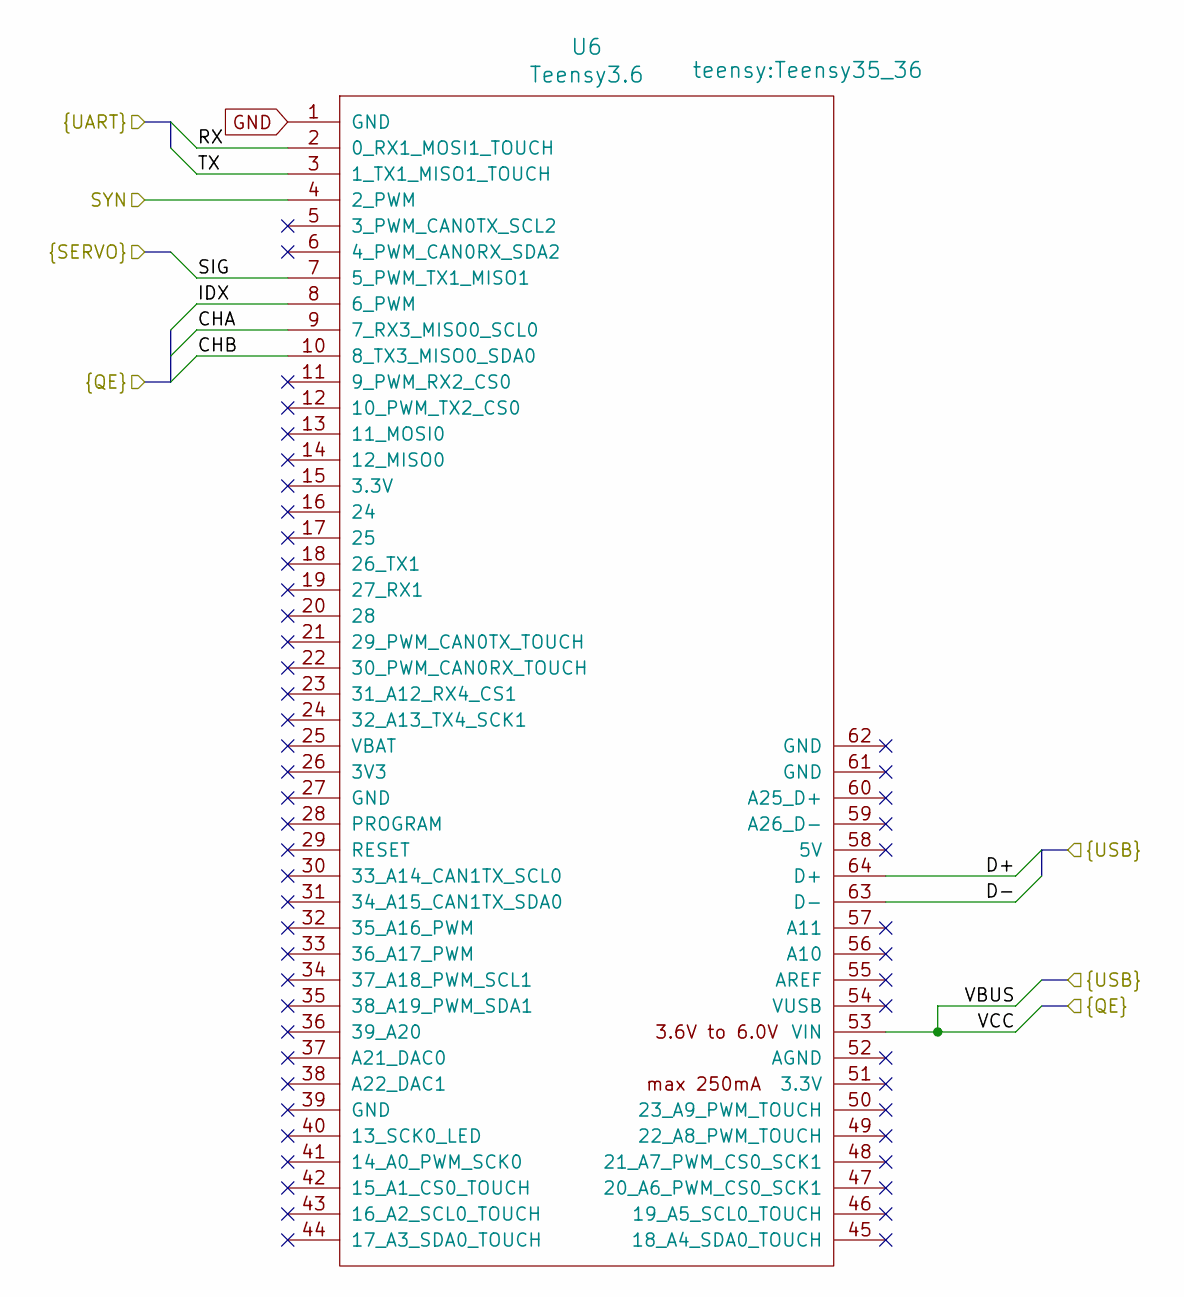
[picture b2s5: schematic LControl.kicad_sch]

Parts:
U6: Teensy3.6; Teensy35_36

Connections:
/Interface Board/USB_L.D+: U6.64 (D+); also elsewhere on the board
/Interface Board/USB_L.D-: U6.63 (D-); also elsewhere on the board
/WIL2.RX: U6.2 (0_RX1_MOSI1_TOUCH); also elsewhere on the board
/WIL2.TX: U6.3 (1_TX1_MISO1_TOUCH); also elsewhere on the board
/WIL3: U6.4 (2_PWM); also elsewhere on the board
/WIL5.SIG: U6.7 (5_PWM_TX1_MISO1); also elsewhere on the board
/WIL6.CHA: U6.9 (7_RX3_MISO0_SCL0); also elsewhere on the board
/WIL6.CHB: U6.10 (8_TX3_MISO0_SDA0); also elsewhere on the board
/WIL6.IDX: U6.8 (6_PWM); also elsewhere on the board
/WIL6.VCC: U6.53 (VIN); also elsewhere on the board
GND: U6.1 (GND); also elsewhere on the board
